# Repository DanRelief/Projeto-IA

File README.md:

# Otimizador de Posicionamento de Componentes em PCBs com Algoritmo Genético (KiCad)

Este repositório contém uma ferramenta de automação desenvolvida em Python para otimizar o posicionamento (*placement*) de componentes eletrônicos em Placas de Circuito Impresso (PCBs). Integrado diretamente à API nativa do **KiCad (`pcbnew`)**, o sistema utiliza um **Algoritmo Genético (AG)** híbrido (com busca local determinística) para distribuir componentes respeitando regras elétricas, integridade de sinal e restrições mecânicas de fabricação.

---

## Visão Geral e Motivação

No projeto de hardware, a disposição física dos componentes impacta diretamente o desempenho eletromagnético, a imunidade a ruídos, a dissipação térmica e a viabilidade de soldagem. O otimizador traduz boas práticas de engenharia de PCB em restrições matemáticas e pesos de atração:

- **Integridade de Sinal e RF (2.4 GHz):** Agrupamento compacto das redes de antena e casamento de impedância (`/ANT_SIG`, `Net-(J1-In)`), mantendo filtros e conectores coaxiais próximos aos pinos de RF do microcontrolador.
- **Estabilidade de Clock e Desacoplamento:** Alta prioridade de proximidade para cristais osciladores (`Y1`, `Y2`) e capacitores de desacoplamento (`C1`–`C4`) junto aos pinos de alimentação e oscilação dos CIs.
- **Proteção na Entrada de Energia:** Ancoragem do fusível de proteção (`F1`) diretamente próximo ao terminal positivo da bateria (`BT2`).
- **Design for Manufacturing (DFM):** Garantia matemática de zero sobreposição física entre corpos/pads (com folga mínima configurável para soldagem) e respeito rigoroso ao contorno real da placa (`Edge.Cuts`).
- **Organização Automática da Serigrafia:** Ocultação de textos de valores poluídos (`Value`) e reposicionamento automático dos designadores (`Reference`) na camada `F.Silkscreen` sem colisões.
- **Relatório de Evolução do Algoritmo:** Registro das gerações executadas, com informações sobre cada componente e as mutações sofridas durante o processo evolutivo.
- **Limpeza Opcional de Serigrafia e Cobre:** Disponibilização de funções para limpeza automática da serigrafia e das trilhas de cobre, permitindo que o usuário escolha quais operações deseja executar.

---

## Tecnologias e Dependências

- **Linguagem:** Python 3.11+
- **EDA / API:** KiCad (v7.0 ou superior, compatível com KiCad 8/9/10) via módulo nativo `pcbnew`
- **Bibliotecas Padrões:** `math`, `random`, `dataclasses`

---

## Arquitetura da Solução

O script foi estruturado em módulos funcionais independentes:

1. **Regras de Engenharia (`BoardRules`):**
   - Separação clara entre **componentes móveis** (`movable_refs`) e **componentes âncora fixos** (`anchor_refs`: microcontrolador `U1`, acelerômetro `U2`, suporte de bateria `BT2` e chaves `SW1`/`SW2`).
   - Pesos individuais por componente, agrupamento mútuo por rede (`group_nets`) e atração de borda (`edge_weights`).
2. **Extração de Contexto da PCB (`Context`):**
   - Leitura dinâmica das coordenadas reais dos *pads* a partir das *nets* da placa (com suporte a mapa de contingência `fallback_map`).
   - Extração do polígono real de contorno (`Edge.Cuts`) para validação geométrica.
3. **Motor Evolutivo (Algoritmo Genético):**
   - **Representação (Cromossomo):** Dicionário mapeando cada componente móvel para $(X, Y, \theta)$, onde $\theta \in \{0^\circ, 90^\circ, 180^\circ, 270^\circ\}$.
   - **Inicialização Gulosa (`create_individual`):** Gera indivíduos iniciais posicionando peças sequencialmente ao redor de seus pinos-alvo sem colisões.
   - **Função de Aptidão (*Fitness*):** Minimiza a soma ponderada das distâncias euclidianas entre pinos conectados e aplica penalidades severas ($10^4 \times \text{violação}$) para invasão de folga mínima (`clearance_mm = 0.35 mm`) ou saída da margem de borda (`edge_margin_mm = 1.50 mm`).
   - **Operadores Genéticos:** Seleção por torneio ($k=3$), elitismo, *crossover* uniforme (50%) e mutação gaussiana com decaimento linear de passo e saltos ocasionais para escapar de ótimos locais.
4. **Refinamento Local e Pós-Processamento:**
   - **Descida por Coordenadas (`local_refinement`):** Ajuste fino determinístico em passos decrescentes ($0.25\text{ mm}$ até $0.01\text{ mm}$) ao final das gerações.
   - **Limpeza de Serigrafia (`tidy_silk`):** Função opcional responsável pela organização dos textos de referência na camada `F.Silkscreen`, evitando colisões e melhorando a legibilidade.
   - **Limpeza de Cobre e Trilhas (`clean_copper`):** Função opcional que permite executar a limpeza de cobre e trilhas da placa, conforme a implementação do script.
   - **Controle pelo Usuário:** As operações de limpeza podem ser ativadas ou desativadas individualmente durante a chamada do algoritmo, por meio de parâmetros booleanos.
---

---

## Parâmetros Configuráveis (`BoardRules` e Execução)

Abaixo estão os principais hiperparâmetros evolutivos e restrições mecânicas que controlam o comportamento do otimizador:

| Parâmetro | Valor Padrão | Local | Descrição |
| :--- | :---: | :---: | :--- |
| `clearance_mm` | `0.35` | `BoardRules` | Folga mínima (mm) entre corpos/pads de componentes adjacentes para garantir soldagem segura sem curtos. |
| `edge_margin_mm` | `1.50` | `BoardRules` | Distância mínima (mm) entre qualquer componente móvel e o contorno externo (`Edge.Cuts`) da placa. |
| `group_weight` | `28.0` | `BoardRules` | Peso de coesão aplicado a componentes que compartilham redes críticas (como linhas de RF e filtros). |
| `init_radius_mm` | `5.0` | `BoardRules` | Raio máximo (mm) ao redor dos pinos-alvo utilizado na geração gulosa da população inicial. |
| `pop_size` | `160` | `run_ga_placement` | Número de indivíduos (layouts candidatos) avaliados simultaneamente em cada geração. |
| `generations` | `250` | `run_ga_placement` | Total de gerações evolutivas executadas antes do refinamento local (*Hill Climbing*). |
| `elite` | `2` | `run_ga_placement` | Quantidade dos melhores indivíduos preservados intactos para a geração seguinte (elitismo). |
| `seed` | `None` | `run_ga_placement` | Semente do gerador pseudoaleatório; defina um inteiro (ex.: `42`) para obter resultados 100% reproduzíveis. |
| `clean_copper` | `True` | `run_ga_placement` | Ativa ou desativa a limpeza de cobre e trilhas. |
| `tidy_silk` | `True` | `run_ga_placement` | Ativa ou desativa a organização automática da serigrafia. |

---

## Guia de Adaptação para Outras Placas

Para reutilizar este otimizador em outro projeto de PCB no KiCad, basta editar a instância `BOARD_RULES` no início do script[cite: 12]:

1. **Defina os componentes móveis e fixos:**
   - Adicione em `movable_refs` os designadores de passivos, cristais, fusíveis e conectores que podem ser reposicionados (`"R1"`, `"C1"`, `"Y1"`, etc.)[cite: 12].
   - Adicione em `anchor_refs` os circuitos integrados principais e componentes mecânicos fixos (`"U1"`, `"BT2"`, `"SW1"`, etc.)[cite: 12].
2. **Configure as atrações e grupos críticos:**
   - Em `attract_to`, associe cada componente móvel ao CI de referência correspondente para evitar atrações cruzadas indesejadas[cite: 12].
   - Em `group_nets`, liste as redes que exigem alta proximidade mútua entre passivos (ex.: casamento de impedância de antena ou filtros LC)[cite: 12].
3. **Ajuste os pesos de prioridade (`weights`):**
   - Atribua valores maiores (ex.: `30.0` a `45.0`) para cristais osciladores, circuitos de RF e proteção de entrada, e valores intermediários (`10.0` a `20.0`) para capacitores de desacoplamento e resistores de *pull-up*[cite: 12].
   - Caso alguma conexão não seja identificada automaticamente pelas *nets* da placa, declare o par `(CI, pino)` correspondente em `fallback_map`[cite: 12].

---

## Como Executar

### Pré-requisitos

- KiCad instalado com suporte ao console de *scripting* Python (`pcbnew`).
- Arquivo da placa (`.kicad_pcb`) devidamente atualizado com a *netlist* do esquemático e o contorno fechado na camada `Edge.Cuts`.

### Execução no Console Python do KiCad

1. Abra o arquivo `.kicad_pcb` no **Editor de PCB do KiCad**.
2. Abra o console interativo em **Ferramentas > Console de Scripting Python**.
3. Execute os comandos abaixo ajustando o caminho para a pasta do seu projeto:

```python
import sys
import importlib
import pcbnew

# Adicione o diretório onde o script está salvo
sys.path.append(r"C:\Caminho\Para\Seu\Projeto")

import script_IA
importlib.reload(script_IA)

# Captura a placa aberta no KiCad e executa a otimização
board = pcbnew.GetBoard()

# Use seed=None para busca estocástica ou fixe um inteiro (ex.: seed=42) para reprodutibilidade
script_IA.run_ga_placement(
    pcbnew.GetBoard(),
    clean_copper=True,
    tidy_silk=True
)

Após a conclusão no console, abra o Visualizador 3D (Alt + 3) ou execute o DRC (Inspecionar > Verificador de Regras de Projeto) para validar as folgas físicas.

## Limitações Conhecidas e Boas Práticas

- **Camada Única (`Top Layer` / `F.Cu`):** A versão atual otimiza apenas componentes posicionados na face superior da placa (`F.Cu`), sem realizar inversão automática (*flip*) para a camada inferior (`B.Cu`).
- **Contorno Fechado (`Edge.Cuts`):** Para que a validação poligonal funcione corretamente, o desenho da borda da placa deve formar um polígono fechado e contínuo; caso contrário, o algoritmo utilizará apenas o retângulo envolvente (*bounding box*).
- **Natureza Estocástica:** Por utilizar operadores probabilísticos, execuções com `seed=None` podem convergir para variações simétricas de custo equivalente. Recomenda-se testar algumas execuções e fixar o valor de `seed` assim que encontrar o layout desejado.
- **Validação Final pelo DRC:** Embora o script garanta folgas entre caixas delimitadoras (*bounding boxes*) dos footprints, sempre execute o **Verificador de Regras de Projeto (DRC)** nativo do KiCad após a execução para validar restrições específicas de máscara de solda e serigrafia.

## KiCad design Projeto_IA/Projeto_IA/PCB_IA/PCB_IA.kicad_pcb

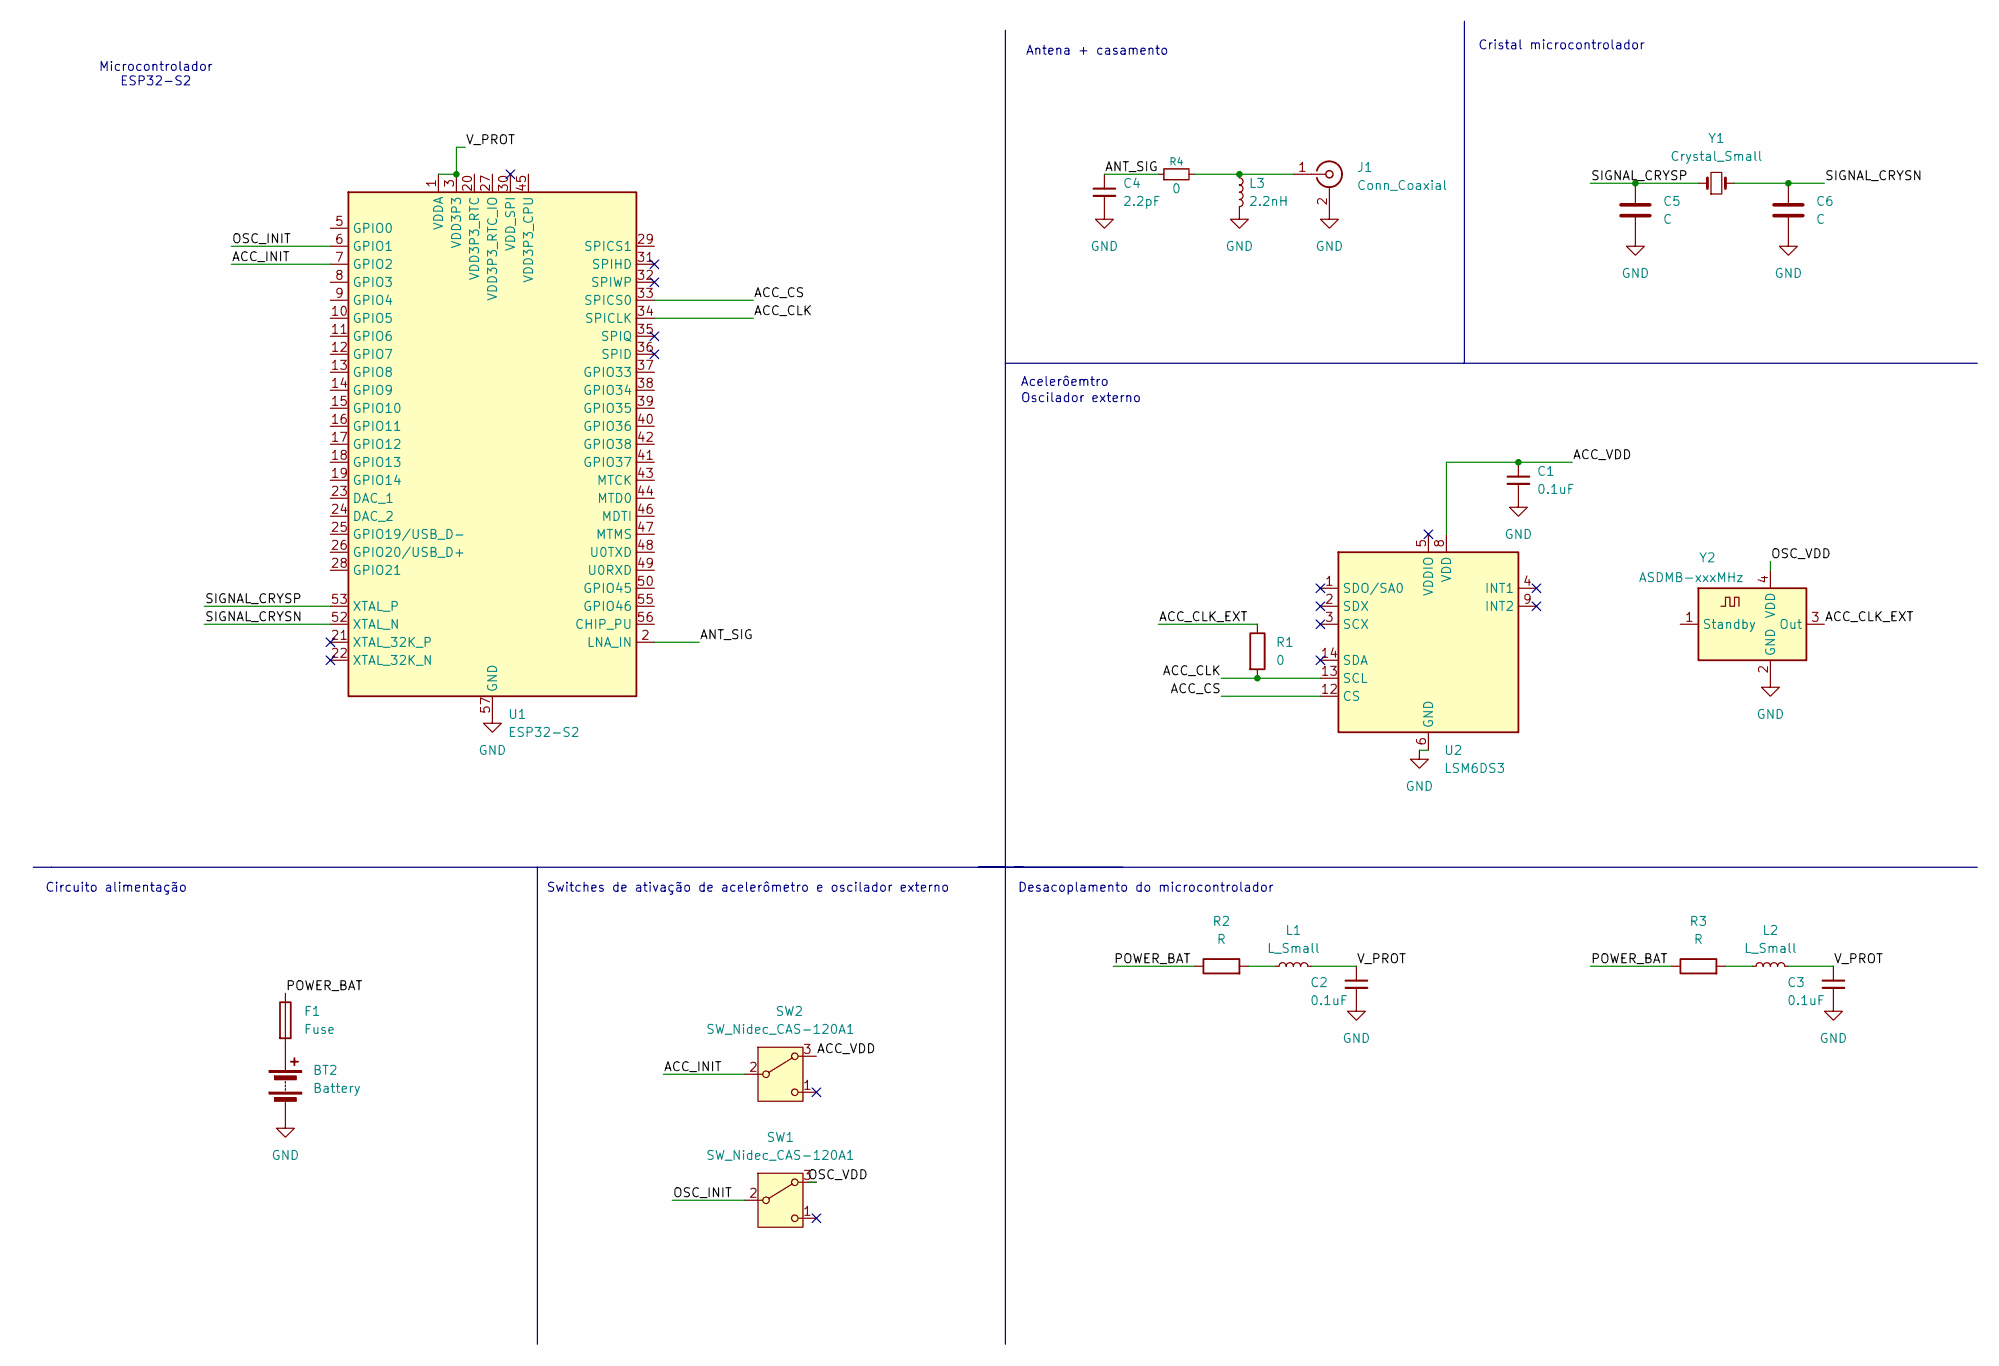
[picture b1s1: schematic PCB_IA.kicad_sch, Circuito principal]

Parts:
BT2: Battery; BatteryHolder_Bulgin_BX0123_1xCR123
C1, C2, C3: 0.1uF; C_01005_0402Metric
C4: 2.2pF; C_01005_0402Metric
C5, C6: C; C_01005_0402Metric
F1: Fuse; Fuse_0402_1005Metric
J1: Conn_Coaxial; U.FL_Hirose_U.FL-R-SMT-1_Vertical
L1, L2: L_Small; L_01005_0402Metric
L3: 2.2nH; L_01005_0402Metric
R1, R4: 0; R_01005_0402Metric
R2, R3: R; R_01005_0402Metric
SW1, SW2: SW_Nidec_CAS-120A1; Nidec_Copal_CAS-120A
U1: ESP32-S2; QFN-56-1EP_7x7mm_P0.4mm_EP4x4mm
U2: LSM6DS3; LGA-14_3x2.5mm_P0.5mm_LayoutBorder3x4y
Y1: Crystal_Small; Crystal_DS10_D1.0mm_L4.3mm_Horizontal
Y2: ASDMB-xxxMHz; Oscillator_SMD_Abracon_ASDMB-4Pin_2.5x2.0mm

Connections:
/ACC_CLK: R1.2, U1.34 (SPICLK), U2.13 (SCL)
/ACC_CLK_EXT: R1.1, Y2.3 (Out)
/ACC_CS: U1.33 (SPICS0), U2.12 (CS)
/ACC_INIT: SW2.2 (B), U1.7 (GPIO2)
/ACC_VDD: C1.1, SW2.3 (A), U2.8 (VDD)
/ANT_SIG: C4.1, R4.1, U1.2 (LNA_IN)
/OSC_INIT: SW1.2 (B), U1.6 (GPIO1)
/OSC_VDD: SW1.3 (A), Y2.4 (VDD)
/POWER_BAT: F1.1, R2.1, R3.1
/SIGNAL_CRYSN: C6.1, U1.52 (XTAL_N), Y1.2
/SIGNAL_CRYSP: C5.1, U1.53 (XTAL_P), Y1.1
/V_PROT: C2.1, C3.1, L1.2, L2.2, U1.1 (VDDA), U1.3 (VDD3P3), U1.4 (VDD3P3), U1.51 (VDDA), U1.54 (VDDA)
GND: BT2.2 (-), C1.2, C2.2, C3.2, C4.2, C5.2, C6.2, J1.2 (Ext), L3.2, U1.57 (GND), U2.6 (GND), U2.7 (GND), Y2.2 (GND)
unnamed: BT2.1 (+), F1.2
unnamed: J1.1 (In), L3.1, R4.2
unnamed: L1.1, R2.2
unnamed: L2.1, R3.2

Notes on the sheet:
Circuito alimentação
Switches de ativação de acelerômetro e oscilador externo
Acelerôemtro
Cristal microcontrolador
Microcontrolador ESP32-S2
Antena + casamento
Desacoplamento do microcontrolador
Oscilador externo

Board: 2 copper layers, 22 parts (0 on the bottom side), 17 nets, no tracks yet.
